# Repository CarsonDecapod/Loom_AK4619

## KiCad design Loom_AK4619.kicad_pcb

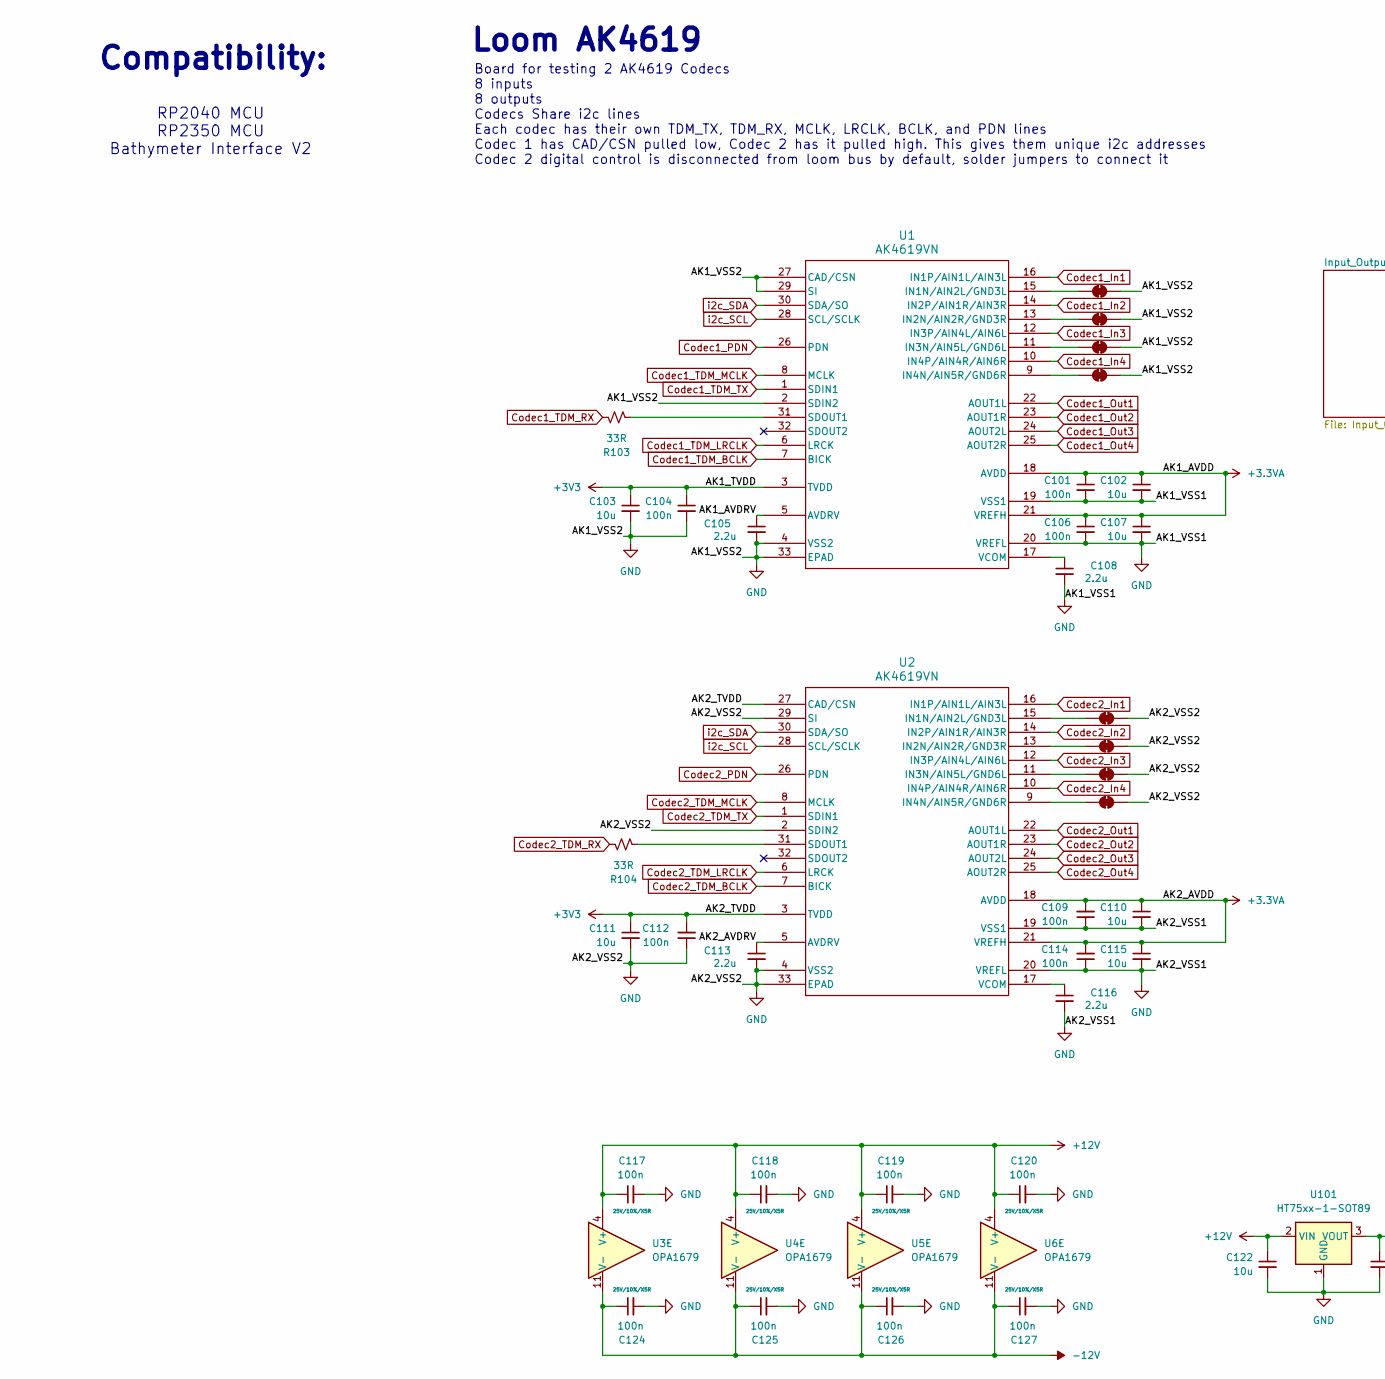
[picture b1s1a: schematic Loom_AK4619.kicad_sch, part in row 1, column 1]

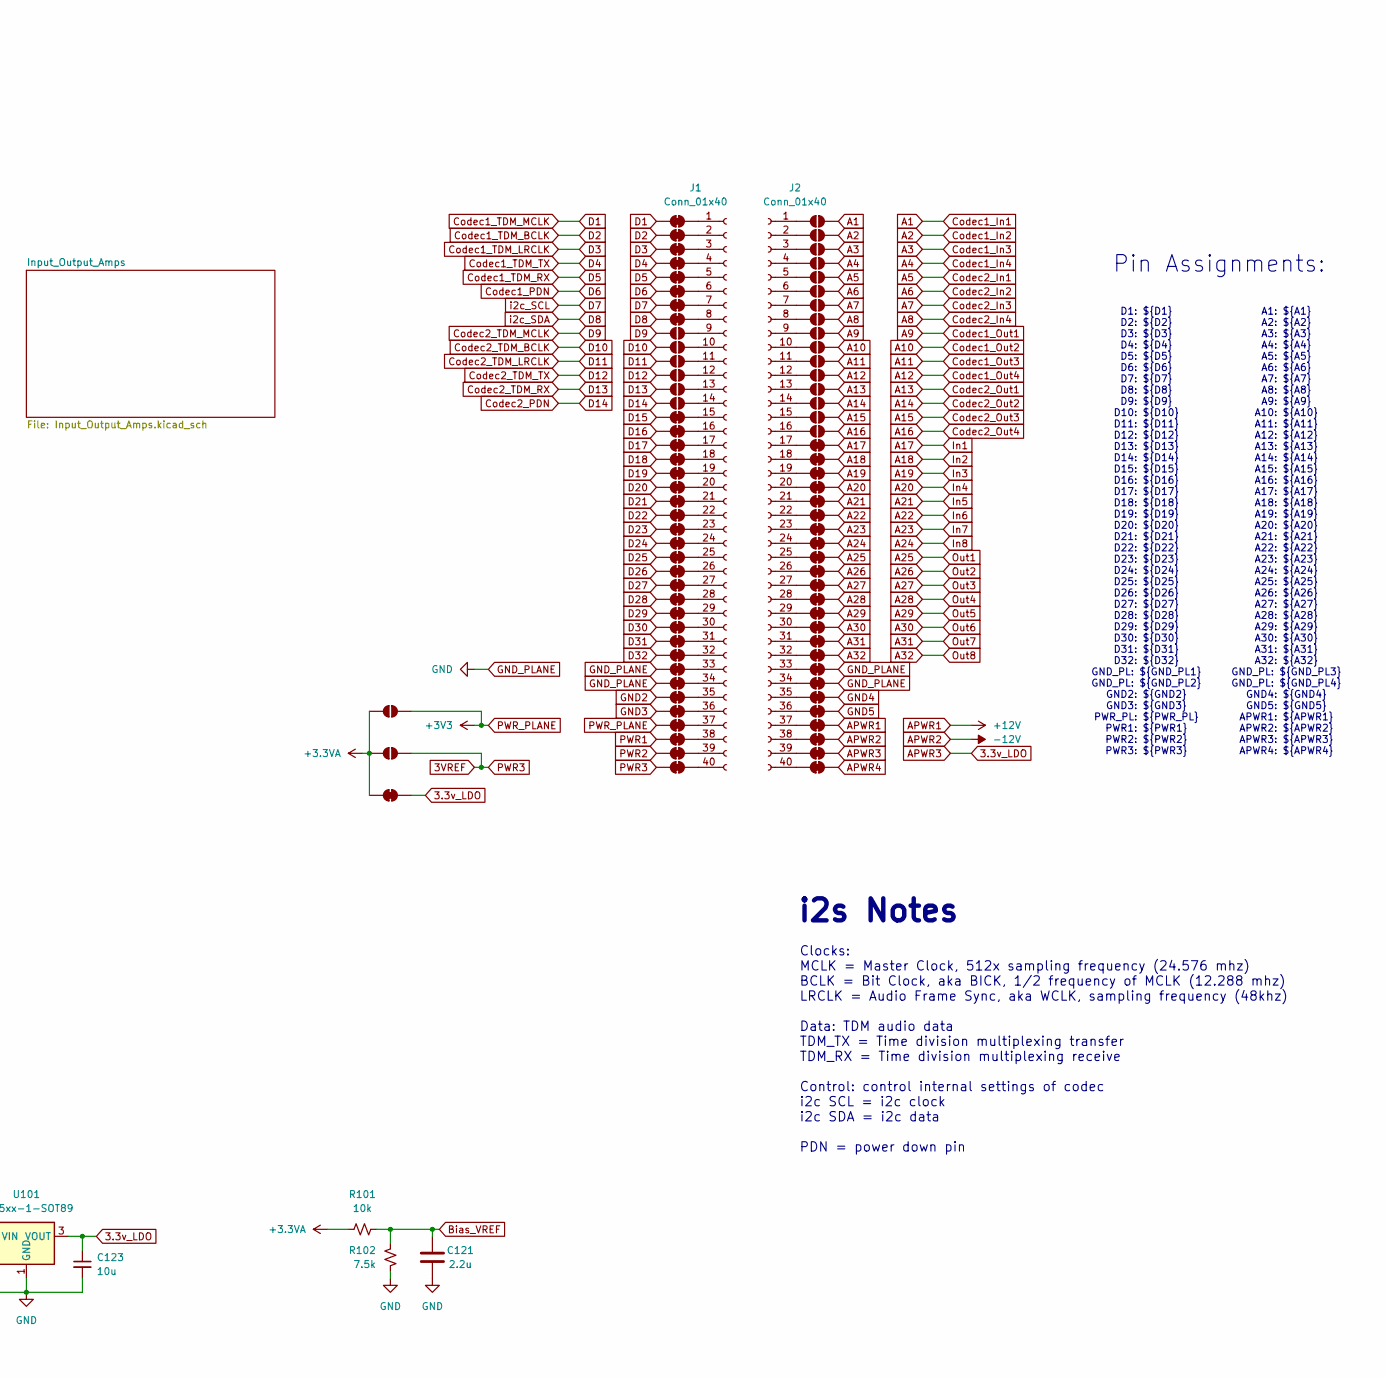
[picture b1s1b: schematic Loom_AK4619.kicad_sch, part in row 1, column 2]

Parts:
C101, C104, C106: 100n; C_0603_HandSolder; Rating 25V/10%/C0G; LCSC C1591
C102, C103, C107, C110, C111, C115, C122, C123: 10u; C_0805_HandSolder; Rating 25V/10%/C0G; LCSC C15850
C105, C108, C113, C116: 2.2u; C_0805_HandSolder; Rating 25V/10%/C0G; LCSC C377773
C109, C112, C114, C117, C118, C119, C120, C124, C125, C126, C127: 100n; C_0603_HandSolder; Rating 25V/10%/X5R; DigiKey 1276-1000-2-ND
C121: 2.2u; C_0805_HandSolder; LCSC C377773
J1, J2: Conn_01x40; PinHeader_1x40_P2.54mm_Vertical
JP101, JP102, JP103, JP104, JP105, JP106, JP107, JP108, JP115, JP116, JP117, JP118, JP119, JP120, JP121, JP122, JP123, JP124, JP125, JP126, JP127, JP128, JP129, JP130, JP131, JP132, JP133, JP134, JP135, JP136, JP137, JP138, JP139, JP140, JP157, JP158, JP159, JP160, JP161, JP162, JP163, JP164, JP165, JP166, JP167, JP168, JP169, JP170, JP171, JP172, JP173, JP174, JP175, JP176, JP177, JP178, JP179, JP180, JP181, JP182, JP183, JP184, JP186, JP187, JP189, JP190, JP191: SolderJumper-2_P1.3mm_Bridged_RoundedPad1.0x1.5mm
JP109, JP110, JP111, JP112, JP113, JP114, JP141, JP142, JP143, JP144, JP145, JP146, JP147, JP148, JP149, JP150, JP151, JP152, JP153, JP154, JP155, JP156, JP185, JP188: SolderJumper_2_Open; SolderJumper-2_P1.3mm_Open_Pad1.0x1.5mm
R101: 10k; R_0603_HandSolder; Rating 100mW/1%/Thin
R102: 7.5k; R_0603_HandSolder; Rating 100mW/1%/Thin
R103, R104: 33R; R_0603_HandSolder; Rating 100mW/1%/Thin
U1, U2: AK4619VN; QFN-32-1EP_5x5mm_P0.5mm_EP3.7x3.7mm_ThermalVias; LCSC C3034747
U3, U4, U5, U6: OPA1679; TSSOP-14_4.4x5mm_P0.65mm; MPN OPA1679
U101: HT75xx-1-SOT89; SOT-89-3

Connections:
3.3v_LDO: C123.1, JP179.1 (A), JP190.1 (A), U101.3 (VOUT)
3VREF: JP140.2 (B), JP188.2 (B)
+3.3VA: C101.1, C102.1, C106.1, C107.1, C109.2, C110.1, C114.2, C115.1, JP185.1 (A), JP188.1 (A), JP190.2 (B), R101.1, U1.18 (AVDD), U1.21 (VREFH), U2.18 (AVDD), U2.21 (VREFH)
/AK1_AVDRV: C105.1, U1.5 (AVDRV)
/AK2_AVDRV: C113.1, U2.5 (AVDRV)
A1: JP141.2 (B), U1.16 (IN1P/AIN1L/AIN3L); also elsewhere on the board
A2: JP142.2 (B), U1.14 (IN2P/AIN1R/AIN3R); also elsewhere on the board
A3: JP143.2 (B), U1.12 (IN3P/AIN4L/AIN6L); also elsewhere on the board
A4: JP144.2 (B), U1.10 (IN4P/AIN4R/AIN6R); also elsewhere on the board
A5: JP145.2 (B), U2.16 (IN1P/AIN1L/AIN3L); also elsewhere on the board
A6: JP146.2 (B), U2.14 (IN2P/AIN1R/AIN3R); also elsewhere on the board
A7: JP147.2 (B), U2.12 (IN3P/AIN4L/AIN6L); also elsewhere on the board
A8: JP148.2 (B), U2.10 (IN4P/AIN4R/AIN6R); also elsewhere on the board
A9: JP149.2 (B), U1.22 (AOUT1L); also elsewhere on the board
A10: JP150.2 (B), U1.23 (AOUT1R); also elsewhere on the board
A11: JP151.2 (B), U1.24 (AOUT2L); also elsewhere on the board
A12: JP152.2 (B), U1.25 (AOUT2R); also elsewhere on the board
A13: JP153.2 (B), U2.22 (AOUT1L); also elsewhere on the board
A14: JP154.2 (B), U2.23 (AOUT1R); also elsewhere on the board
A15: JP155.2 (B), U2.24 (AOUT2L); also elsewhere on the board
A16: JP156.2 (B), U2.25 (AOUT2R); also elsewhere on the board
A17: JP157.1 (A); also elsewhere on the board
A18: JP158.1 (A); also elsewhere on the board
A19: JP159.1 (A); also elsewhere on the board
A20: JP160.1 (A); also elsewhere on the board
A21: JP161.1 (A); also elsewhere on the board
A22: JP162.1 (A); also elsewhere on the board
A23: JP163.1 (A); also elsewhere on the board
A24: JP164.1 (A); also elsewhere on the board
A25: JP165.1 (A); also elsewhere on the board
A26: JP166.1 (A); also elsewhere on the board
A27: JP167.1 (A); also elsewhere on the board
A28: JP168.1 (A); also elsewhere on the board
A29: JP169.1 (A); also elsewhere on the board
A30: JP170.1 (A); also elsewhere on the board
A31: JP171.1 (A); also elsewhere on the board
A32: JP172.1 (A); also elsewhere on the board
APWR1: C117.1, C118.1, C119.1, C120.1, C122.1, JP177.1 (A), U3.4 (V+), U4.4 (V+), U5.4 (V+), U6.4 (V+), U101.2 (VIN)
APWR2: C124.1, C125.1, C126.1, C127.1, JP178.1 (A), U3.11 (V-), U4.11 (V-), U5.11 (V-), U6.11 (V-)
APWR4: JP180.1 (A)
Bias_VREF: C121.2, R101.2, R102.2, U3.3 (+), U3.5 (+), U3.10 (+), U4.3 (+), U4.5 (+), U4.10 (+), U5.5 (+), U5.10 (+), U5.12 (+), U6.5 (+), U6.10 (+), U6.12 (+); also elsewhere on the board
Codec1_PDN: JP106.2 (B), U1.26 (PDN)
Codec1_TDM_BCLK: JP102.2 (B), U1.7 (BICK)
Codec1_TDM_LRCLK: JP103.2 (B), U1.6 (LRCK)
Codec1_TDM_MCLK: JP101.2 (B), U1.8 (MCLK)
Codec1_TDM_RX: JP105.2 (B), R103.1
Codec1_TDM_TX: JP104.2 (B), U1.1 (SDIN1)
Codec2_PDN: JP114.1 (A), U2.26 (PDN)
Codec2_TDM_BCLK: JP110.1 (A), U2.7 (BICK)
Codec2_TDM_LRCLK: JP111.1 (A), U2.6 (LRCK)
Codec2_TDM_MCLK: JP109.1 (A), U2.8 (MCLK)
Codec2_TDM_RX: JP113.1 (A), R104.1
Codec2_TDM_TX: JP112.1 (A), U2.1 (SDIN1)
D7: JP107.2 (B), U1.28 (SCL/SCLK), U2.28 (SCL/SCLK)
D8: JP108.2 (B), U1.30 (SDA/SO), U2.30 (SDA/SO)
D15: JP115.2 (B)
D16: JP116.2 (B)
D17: JP117.2 (B)
D18: JP118.2 (B)
D19: JP119.2 (B)
D20: JP120.2 (B)
D21: JP121.2 (B)
D22: JP122.2 (B)
D23: JP123.2 (B)
D24: JP124.2 (B)
D25: JP125.2 (B)
D26: JP126.2 (B)
D27: JP127.2 (B)
D28: JP128.2 (B)
D29: JP129.2 (B)
D30: JP130.2 (B)
D31: JP131.2 (B)
D32: JP132.2 (B)
GND2: JP135.2 (B)
GND3: JP136.2 (B)
GND4: JP175.1 (A)
GND5: JP176.1 (A)
GND_PLANE: C101.2, C102.2, C103.2, C104.2, C105.2, C106.2, C107.2, C108.2, C109.1, C110.2, C111.2, C112.1, C113.2, C114.1, C115.2, C116.2, C117.2, C118.2, C119.2, C120.2, C121.1, C122.2, C123.2, C124.2, C125.2, C126.2, C127.2, JP133.2 (B), JP134.2 (B), JP173.1 (A), JP174.1 (A), JP181.1 (A), JP182.1 (A), JP183.1 (A), JP184.1 (A), JP186.1 (A), JP187.1 (A), JP189.1 (A), JP191.1 (A), R102.1, U1.2 (SDIN2), U1.4 (VSS2), U1.19 (VSS1), U1.20 (VREFL), U1.27 (CAD/CSN), U1.29 (SI), U1.33 (EPAD), U2.2 (SDIN2), U2.4 (VSS2), U2.19 (VSS1), U2.20 (VREFL), U2.29 (SI), U2.33 (EPAD), U101.1 (GND)
unnamed 78: U3.1; also elsewhere on the board
unnamed 79: U3.7; also elsewhere on the board
unnamed 80: U3.8; also elsewhere on the board
unnamed 82: U4.1; also elsewhere on the board
unnamed 83: U4.7; also elsewhere on the board
unnamed 84: U4.8; also elsewhere on the board
unnamed 87: U5.7; also elsewhere on the board
unnamed 88: U5.8; also elsewhere on the board
unnamed 89: U5.14; also elsewhere on the board
unnamed 91: U6.7; also elsewhere on the board
unnamed 92: U6.8; also elsewhere on the board
unnamed 93: U6.14; also elsewhere on the board
unnamed: J1.1, JP101.1 (A)
unnamed: J1.2, JP102.1 (A)
unnamed: J1.3, JP103.1 (A)
unnamed: J1.4, JP104.1 (A)
unnamed: J1.5, JP105.1 (A)
unnamed: J1.6, JP106.1 (A)
unnamed: J1.7, JP107.1 (A)
unnamed: J1.8, JP108.1 (A)
unnamed: J1.9, JP109.2 (B)
unnamed: J1.10, JP110.2 (B)
unnamed: J1.11, JP111.2 (B)
unnamed: J1.12, JP112.2 (B)
unnamed: J1.13, JP113.2 (B)
unnamed: J1.14, JP114.2 (B)
unnamed: J1.15, JP115.1 (A)
unnamed: J1.16, JP116.1 (A)
unnamed: J1.17, JP117.1 (A)
unnamed: J1.18, JP118.1 (A)
unnamed: J1.19, JP119.1 (A)
unnamed: J1.20, JP120.1 (A)
unnamed: J1.21, JP121.1 (A)
unnamed: J1.22, JP122.1 (A)
unnamed: J1.23, JP123.1 (A)
unnamed: J1.24, JP124.1 (A)
unnamed: J1.25, JP125.1 (A)
unnamed: J1.26, JP126.1 (A)
unnamed: J1.27, JP127.1 (A)
unnamed: J1.28, JP128.1 (A)
unnamed: J1.29, JP129.1 (A)
unnamed: J1.30, JP130.1 (A)
unnamed: J1.31, JP131.1 (A)
unnamed: J1.32, JP132.1 (A)
unnamed: J1.33, JP133.1 (A)
unnamed: J1.34, JP134.1 (A)
unnamed: J1.35, JP135.1 (A)
unnamed: J1.36, JP136.1 (A)
unnamed: J1.37, JP137.1 (A)
unnamed: J1.38, JP138.1 (A)
unnamed: J1.39, JP139.1 (A)
unnamed: J1.40, JP140.1 (A)
unnamed: J2.1, JP141.1 (A)
unnamed: J2.2, JP142.1 (A)
unnamed: J2.3, JP143.1 (A)
unnamed: J2.4, JP144.1 (A)
unnamed: J2.5, JP145.1 (A)
unnamed: J2.6, JP146.1 (A)
unnamed: J2.7, JP147.1 (A)
unnamed: J2.8, JP148.1 (A)
unnamed: J2.9, JP149.1 (A)
unnamed: J2.10, JP150.1 (A)
unnamed: J2.11, JP151.1 (A)
unnamed: J2.12, JP152.1 (A)
unnamed: J2.13, JP153.1 (A)
unnamed: J2.14, JP154.1 (A)
unnamed: J2.15, JP155.1 (A)
unnamed: J2.16, JP156.1 (A)
unnamed: J2.17, JP157.2 (B)
unnamed: J2.18, JP158.2 (B)
unnamed: J2.19, JP159.2 (B)
unnamed: J2.20, JP160.2 (B)
unnamed: J2.21, JP161.2 (B)
unnamed: J2.22, JP162.2 (B)
unnamed: J2.23, JP163.2 (B)
unnamed: J2.24, JP164.2 (B)
unnamed: J2.25, JP165.2 (B)
unnamed: J2.26, JP166.2 (B)
unnamed: J2.27, JP167.2 (B)
unnamed: J2.28, JP168.2 (B)
unnamed: J2.29, JP169.2 (B)
unnamed: J2.30, JP170.2 (B)
unnamed: J2.31, JP171.2 (B)
unnamed: J2.32, JP172.2 (B)
unnamed: J2.33, JP173.2 (B)
unnamed: J2.34, JP174.2 (B)
unnamed: J2.35, JP175.2 (B)
unnamed: J2.36, JP176.2 (B)
unnamed: J2.37, JP177.2 (B)
unnamed: J2.38, JP178.2 (B)
unnamed: J2.39, JP179.2 (B)
unnamed: J2.40, JP180.2 (B)
unnamed: JP181.2 (B), U1.15 (IN1N/AIN2L/GND3L)
unnamed: JP182.2 (B), U1.13 (IN2N/AIN2R/GND3R)
unnamed: JP183.2 (B), U1.11 (IN3N/AIN5L/GND6L)
unnamed: JP184.2 (B), U1.9 (IN4N/AIN5R/GND6R)
unnamed: JP186.2 (B), U2.15 (IN1N/AIN2L/GND3L)
unnamed: JP187.2 (B), U2.13 (IN2N/AIN2R/GND3R)
unnamed: JP189.2 (B), U2.11 (IN3N/AIN5L/GND6L)
unnamed: JP191.2 (B), U2.9 (IN4N/AIN5R/GND6R)
unnamed: R103.2, U1.31 (SDOUT1)
unnamed: C108.1, U1.17 (VCOM)
unnamed: R104.2, U2.31 (SDOUT1)
unnamed: C116.1, U2.17 (VCOM)
unnamed 186: U3.2 (-); also elsewhere on the board
unnamed 187: U3.6 (-); also elsewhere on the board
unnamed 188: U3.9 (-); also elsewhere on the board
unnamed 190: U4.2 (-); also elsewhere on the board
unnamed 191: U4.6 (-); also elsewhere on the board
unnamed 192: U4.9 (-); also elsewhere on the board
unnamed 195: U5.6 (-); also elsewhere on the board
unnamed 196: U5.9 (-); also elsewhere on the board
unnamed 197: U5.13 (-); also elsewhere on the board
unnamed 199: U6.6 (-); also elsewhere on the board
unnamed 200: U6.9 (-); also elsewhere on the board
unnamed 201: U6.13 (-); also elsewhere on the board
PWR1: JP138.2 (B)
PWR2: JP139.2 (B)
PWR_PLANE: C103.1, C104.1, C111.1, C112.2, JP137.2 (B), JP185.2 (B), U1.3 (TVDD), U2.3 (TVDD), U2.27 (CAD/CSN)

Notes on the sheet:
Pin Assignments:
A1: ${A1} A2: ${A2} A3: ${A3} A4: ${A4} A5: ${A5} A6: ${A6} A7: ${A7} A8: ${A8} A9: ${A9} A10: ${A10} A11: ${A11} A12: ${A12} A13: ${A13} A14: ${A14} A15: ${A15} A16: ${A16} A17: ${A17} A18: ${A18} A19: ${A19} A20: ${A20} A21: ${A21} A22: ${A22} A23: ${A23} A24: ${A24} A25: ${A25} A26: ${A26} A27: 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
Clocks: MCLK = Master Clock, 512x sampling frequency (24.576 mhz) BCLK = Bit Clock, aka BICK, 1/2 frequency of MCLK (12.288 mhz) LRCLK = Audio Frame Sync, aka WCLK, sampling frequency (48khz) Data: TDM audio data TDM_TX = Time division multiplexing transfer TDM_RX = Time division multiplexing recei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
Loom AK4619
i2s Notes
Board for testing 2 AK4619 Codecs 8 inputs 8 outputs Codecs Share i2c lines Each codec has their own TDM_TX, TDM_RX, MCLK, LRCLK, BCLK, and PDN lines Codec 1 has CAD/CSN pulled low, Codec 2 has it pulled high. This gives them unique i2c addresses Codec 2 digital control is disconnected from loom bu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
D1: ${D1} D2: ${D2} D3: ${D3} D4: ${D4} D5: ${D5} D6: ${D6} D7: ${D7} D8: ${D8} D9: ${D9} D10: ${D10} D11: ${D11} D12: ${D12} D13: ${D13} D14: ${D14} D15: ${D15} D16: ${D16} D17: ${D17} D18: ${D18} D19: ${D19} D20: ${D20} D21: ${D21} D22: ${D22} D23: ${D23} D24: ${D24} D25: ${D25} D26: ${D26} D27: 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
Compatibility:
RP2040 MCU RP2350 MCU Bathymeter Interface V2

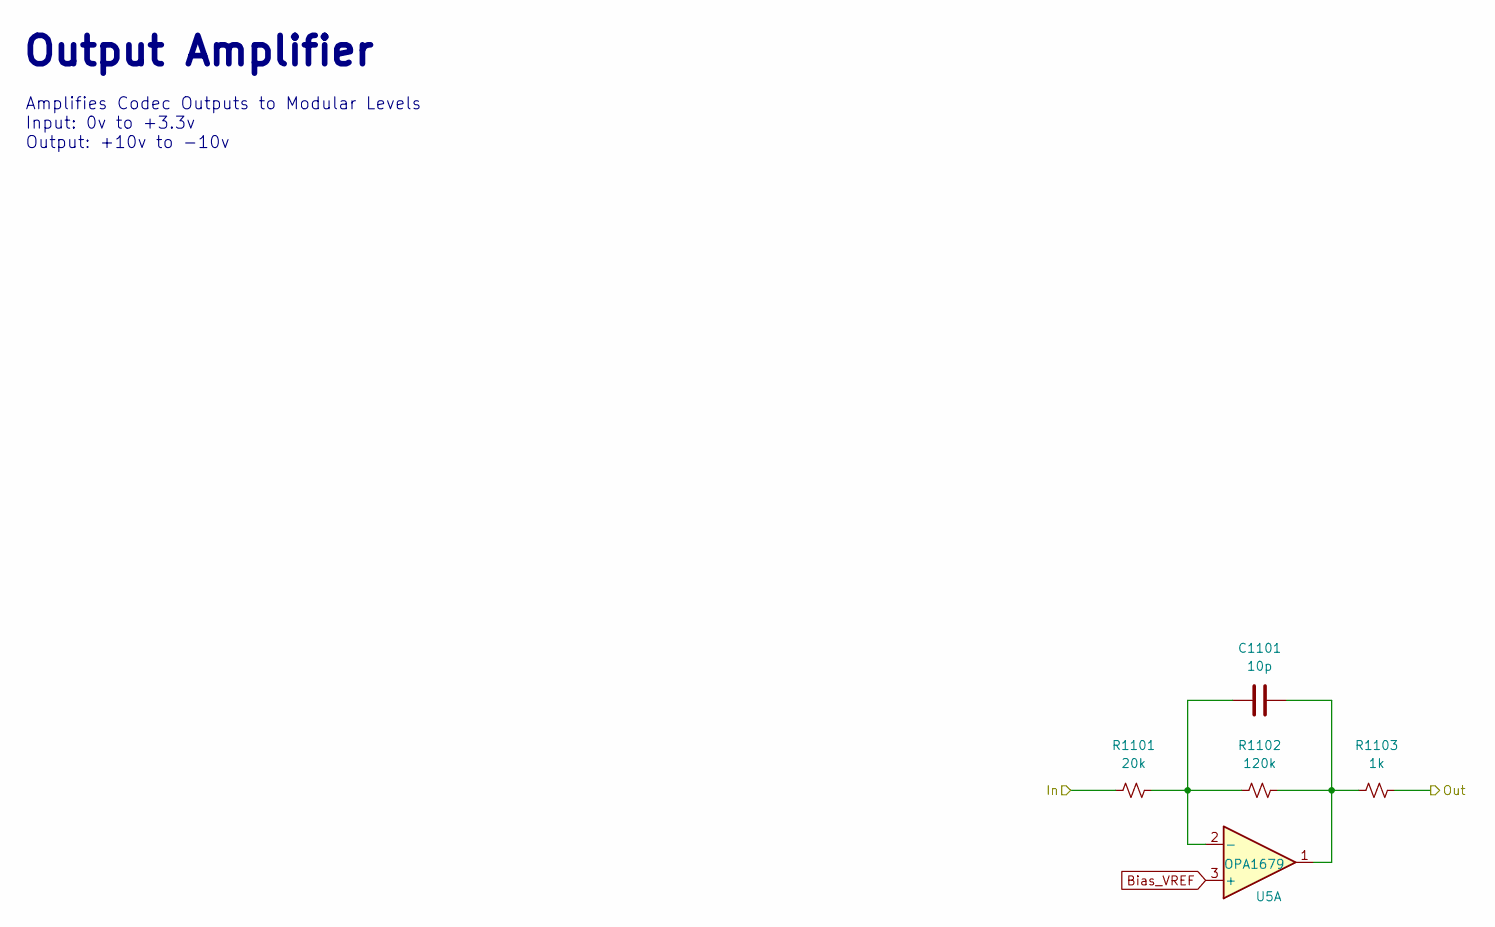
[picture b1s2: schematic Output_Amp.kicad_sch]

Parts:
C1101: 10p; C_0603_HandSolder; LCSC C1634
R1101: 20k; R_0603_HandSolder; Rating 100mW/1%/Thin
R1102: 120k; R_0603_HandSolder; Rating 100mW/1%/Thin
R1103: 1k; R_0603_HandSolder; Rating 100mW/1%/Thin
U5: OPA1679; TSSOP-14_4.4x5mm_P0.65mm; MPN OPA1679

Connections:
A9: R1101.1; also elsewhere on the board
A25: R1103.2; also elsewhere on the board
Bias_VREF: U5.3 (+), U5.5 (+), U5.10 (+), U5.12 (+); also elsewhere on the board
unnamed: C1101.1, R1102.2, R1103.1, U5.1
unnamed 87: U5.7; also elsewhere on the board
unnamed 88: U5.8; also elsewhere on the board
unnamed 89: U5.14; also elsewhere on the board
unnamed: C1101.2, R1101.2, R1102.1, U5.2 (-)
unnamed 195: U5.6 (-); also elsewhere on the board
unnamed 196: U5.9 (-); also elsewhere on the board
unnamed 197: U5.13 (-); also elsewhere on the board

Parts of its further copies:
C1201, C1301, C1401, C1501, C1601, C1701, C1801: 10p; C_0603_HandSolder; LCSC C1634
R1201, R1301, R1401, R1501, R1601, R1701, R1801: 20k; R_0603_HandSolder; Rating 100mW/1%/Thin
R1202, R1302, R1402, R1502, R1602, R1702, R1802: 120k; R_0603_HandSolder; Rating 100mW/1%/Thin
R1203, R1303, R1403, R1503, R1603, R1703, R1803: 1k; R_0603_HandSolder; Rating 100mW/1%/Thin

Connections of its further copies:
A10: R1201.1; also elsewhere on the board
A11: R1301.1; also elsewhere on the board
A12: R1401.1; also elsewhere on the board
A13: R1501.1; also elsewhere on the board
A14: R1601.1; also elsewhere on the board
A15: R1701.1; also elsewhere on the board
A16: R1801.1; also elsewhere on the board
A26: R1203.2; also elsewhere on the board
A27: R1303.2; also elsewhere on the board
A28: R1403.2; also elsewhere on the board
A29: R1503.2; also elsewhere on the board
A30: R1603.2; also elsewhere on the board
A31: R1703.2; also elsewhere on the board
A32: R1803.2; also elsewhere on the board
unnamed 87: C1201.1, R1202.2, R1203.1; also elsewhere on the board
unnamed 88: C1301.1, R1302.2, R1303.1; also elsewhere on the board
unnamed 89: C1401.1, R1402.2, R1403.1; also elsewhere on the board
unnamed 90: C1501.1, R1502.2, R1503.1; also elsewhere on the board
unnamed 91: C1601.1, R1602.2, R1603.1; also elsewhere on the board
unnamed 92: C1701.1, R1702.2, R1703.1; also elsewhere on the board
unnamed 93: C1801.1, R1802.2, R1803.1; also elsewhere on the board
unnamed 195: C1201.2, R1201.2, R1202.1; also elsewhere on the board
unnamed 196: C1301.2, R1301.2, R1302.1; also elsewhere on the board
unnamed 197: C1401.2, R1401.2, R1402.1; also elsewhere on the board
unnamed 198: C1501.2, R1501.2, R1502.1; also elsewhere on the board
unnamed 199: C1601.2, R1601.2, R1602.1; also elsewhere on the board
unnamed 200: C1701.2, R1701.2, R1702.1; also elsewhere on the board
unnamed 201: C1801.2, R1801.2, R1802.1; also elsewhere on the board

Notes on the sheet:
Amplifies Codec Outputs to Modular Levels Input: 0v to +3.3v Output: +10v to -10v
Output Amplifier

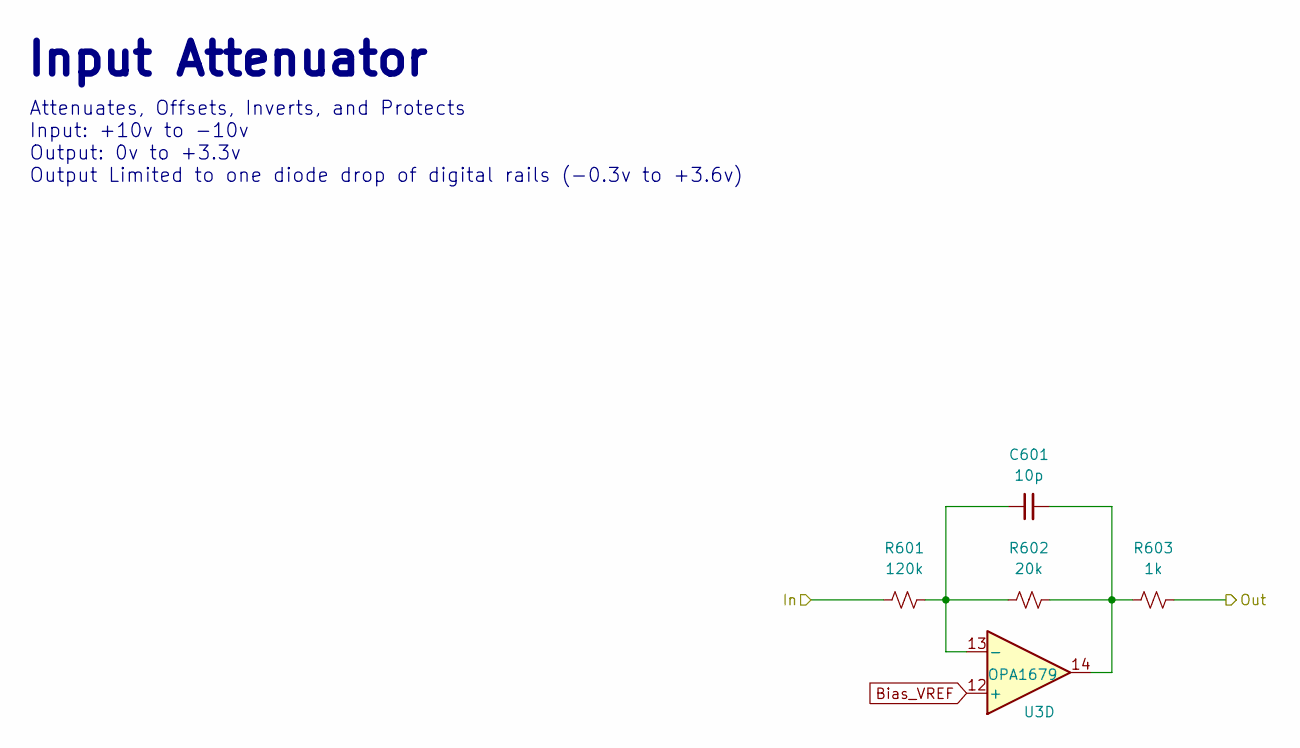
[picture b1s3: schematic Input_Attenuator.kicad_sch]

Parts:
C601: 10p; C_0603_HandSolder; Rating 25V/10%/C0G; LCSC C1634
R601: 120k; R_0603_HandSolder; Rating 100mW/1%/Thin
R602: 20k; R_0603_HandSolder; Rating 100mW/1%/Thin
R603: 1k; R_0603_HandSolder; Rating 100mW/1%/Thin
U3: OPA1679; TSSOP-14_4.4x5mm_P0.65mm; MPN OPA1679

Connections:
A4: R603.2; also elsewhere on the board
A20: R601.1; also elsewhere on the board
Bias_VREF: U3.3 (+), U3.5 (+), U3.10 (+), U3.12 (+); also elsewhere on the board
unnamed 78: U3.1; also elsewhere on the board
unnamed 79: U3.7; also elsewhere on the board
unnamed 80: U3.8; also elsewhere on the board
unnamed: C601.2, R602.2, R603.1, U3.14
unnamed 186: U3.2 (-); also elsewhere on the board
unnamed 187: U3.6 (-); also elsewhere on the board
unnamed 188: U3.9 (-); also elsewhere on the board
unnamed: C601.1, R601.2, R602.1, U3.13 (-)

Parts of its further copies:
C301, C401, C501, C701, C801, C901, C1001: 10p; C_0603_HandSolder; Rating 25V/10%/C0G; LCSC C1634
R301, R401, R501, R701, R801, R901, R1001: 120k; R_0603_HandSolder; Rating 100mW/1%/Thin
R302, R402, R502, R702, R802, R902, R1002: 20k; R_0603_HandSolder; Rating 100mW/1%/Thin
R303, R403, R503, R703, R803, R903, R1003: 1k; R_0603_HandSolder; Rating 100mW/1%/Thin

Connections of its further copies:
A1: R303.2; also elsewhere on the board
A2: R403.2; also elsewhere on the board
A3: R503.2; also elsewhere on the board
A5: R703.2; also elsewhere on the board
A6: R803.2; also elsewhere on the board
A7: R903.2; also elsewhere on the board
A8: R1003.2; also elsewhere on the board
A17: R301.1; also elsewhere on the board
A18: R401.1; also elsewhere on the board
A19: R501.1; also elsewhere on the board
A21: R701.1; also elsewhere on the board
A22: R801.1; also elsewhere on the board
A23: R901.1; also elsewhere on the board
A24: R1001.1; also elsewhere on the board
unnamed 78: C301.2, R302.2, R303.1; also elsewhere on the board
unnamed 79: C401.2, R402.2, R403.1; also elsewhere on the board
unnamed 80: C501.2, R502.2, R503.1; also elsewhere on the board
unnamed 82: C701.2, R702.2, R703.1; also elsewhere on the board
unnamed 83: C801.2, R802.2, R803.1; also elsewhere on the board
unnamed 84: C901.2, R902.2, R903.1; also elsewhere on the board
unnamed 85: C1001.2, R1002.2, R1003.1; also elsewhere on the board
unnamed 186: C301.1, R301.2, R302.1; also elsewhere on the board
unnamed 187: C401.1, R401.2, R402.1; also elsewhere on the board
unnamed 188: C501.1, R501.2, R502.1; also elsewhere on the board
unnamed 190: C701.1, R701.2, R702.1; also elsewhere on the board
unnamed 191: C801.1, R801.2, R802.1; also elsewhere on the board
unnamed 192: C901.1, R901.2, R902.1; also elsewhere on the board
unnamed 193: C1001.1, R1001.2, R1002.1; also elsewhere on the board

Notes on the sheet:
Attenuates, Offsets, Inverts, and Protects Input: +10v to -10v Output: 0v to +3.3v Output Limited to one diode drop of digital rails (-0.3v to +3.6v)
Input Attenuator

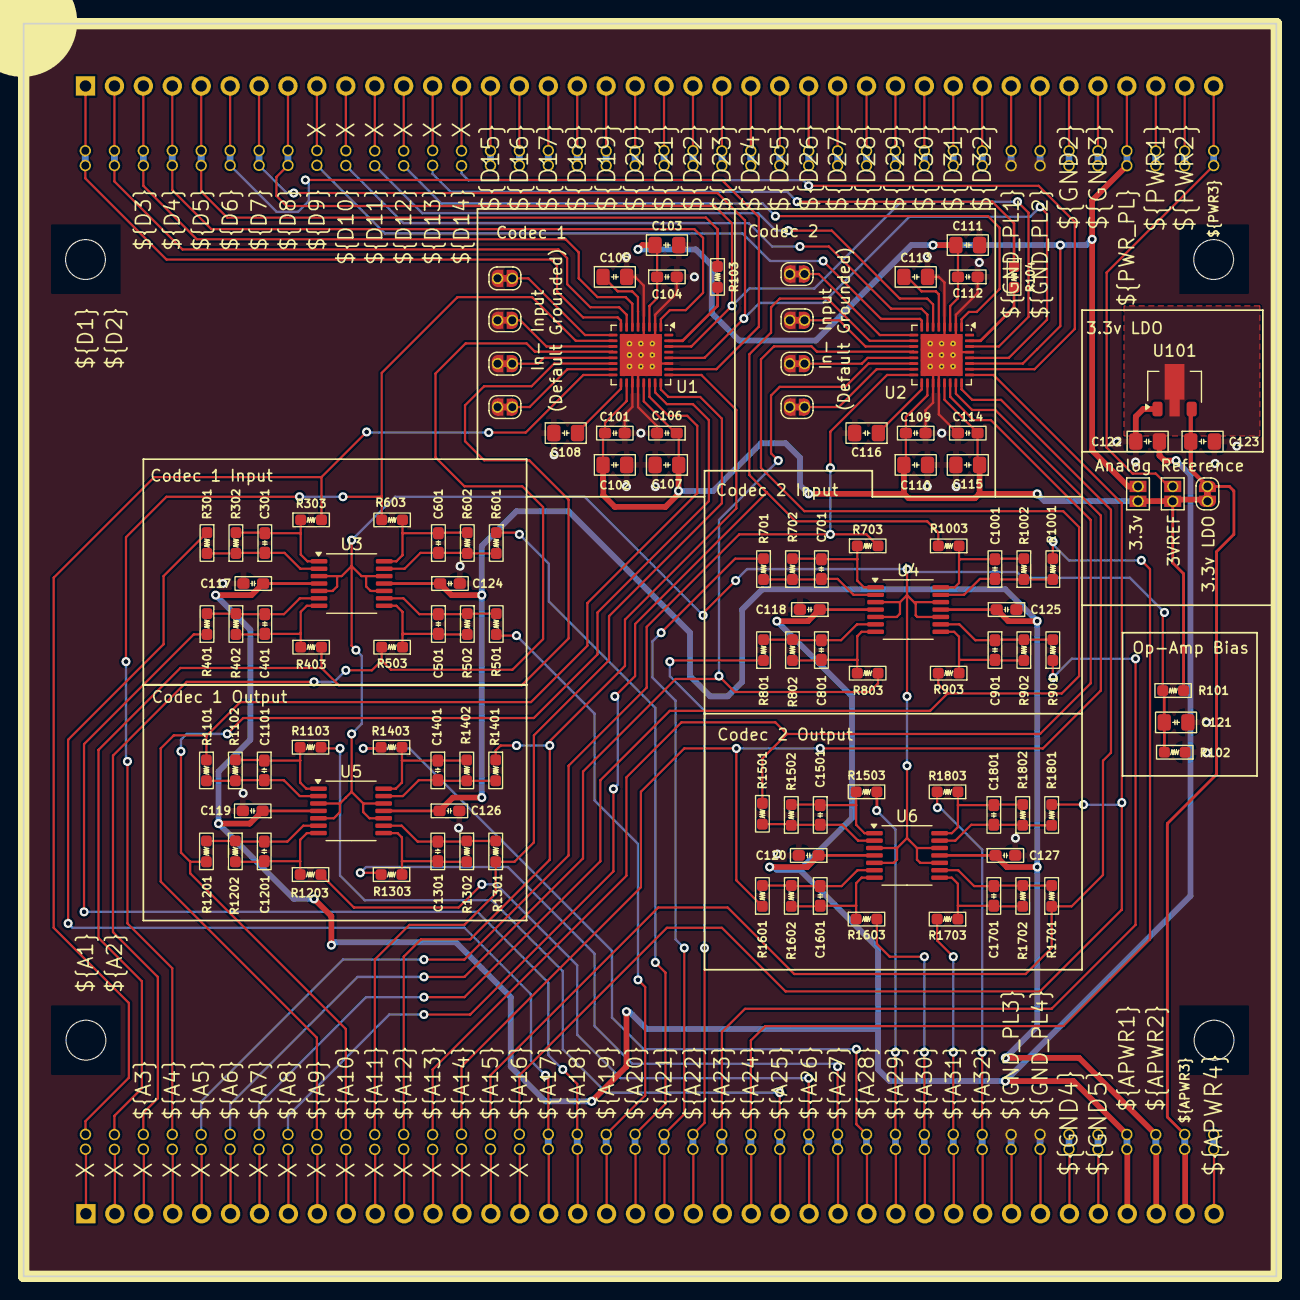
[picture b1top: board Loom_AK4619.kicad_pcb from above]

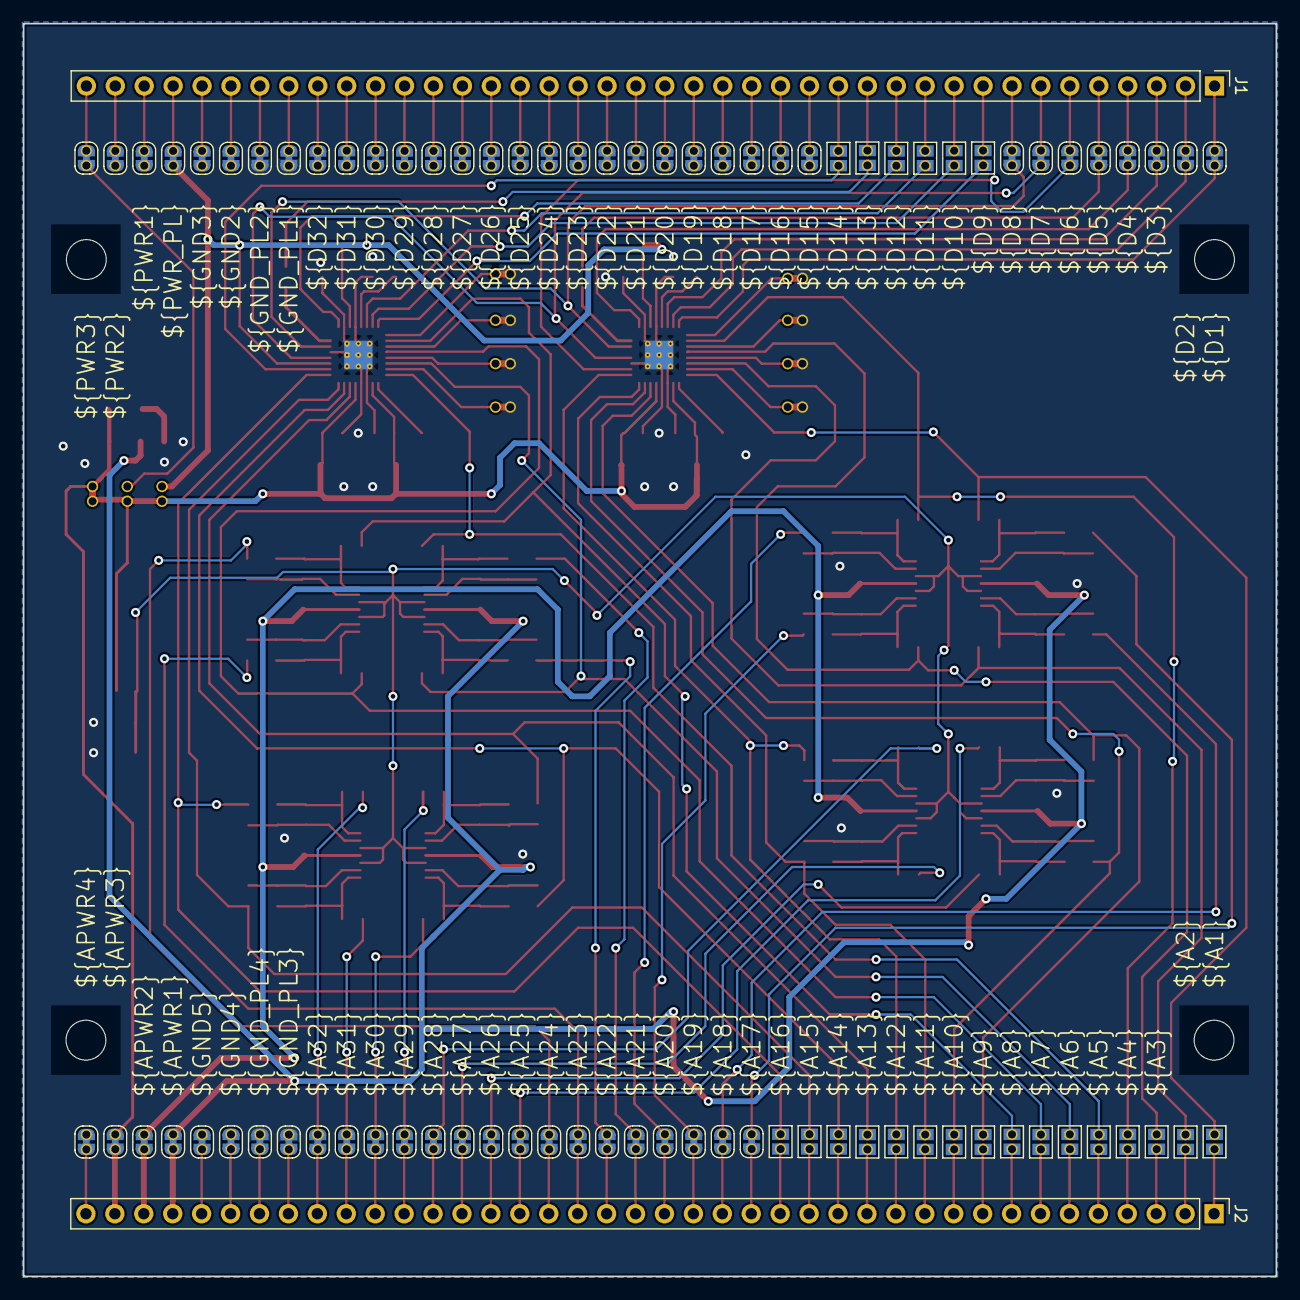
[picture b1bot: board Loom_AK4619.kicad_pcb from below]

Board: 2 copper layers, 110.0 x 110.0 mm, 195 parts (82 on the bottom side), 180 nets.

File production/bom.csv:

Designator,Footprint,Quantity,Value,LCSC Part #
"C1001, C1101, C1201, C1301, C1401, C1501, C1601, C1701, C1801, C301, C401, C501, C601, C701, C801, C901",C_0603_HandSolder,16,10p,C1634
"C101, C104, C106, C109, C112, C114, C117, C118, C119, C120, C124, C125, C126, C127",C_0603_HandSolder,14,100n,C1591
"C102, C103, C107, C110, C111, C115, C122, C123",C_0805_HandSolder,8,10u,C15850
"C105, C108, C113, C116, C121",C_0805_HandSolder,5,2.2u,C377773
"J1, J2",PinHeader_1x40_P2.54mm_Vertical,2,Conn_01x40,
"R1001, R1102, R1202, R1302, R1402, R1502, R1602, R1702, R1802, R301, R401, R501, R601, R701, R801, R901",R_0603_HandSolder,16,120k,
"R1002, R1101, R1201, R1301, R1401, R1501, R1601, R1701, R1801, R302, R402, R502, R602, R702, R802, R902",R_0603_HandSolder,16,20k,
"R1003, R1103, R1203, R1303, R1403, R1503, R1603, R1703, R1803, R303, R403, R503, R603, R703, R803, R903",R_0603_HandSolder,16,1k,
R101,R_0603_HandSolder,1,10k,
R102,R_0603_HandSolder,1,7.5k,
"R103, R104",R_0603_HandSolder,2,33R,
"U1, U2",QFN-32-1EP_5x5mm_P0.5mm_EP3.7x3.7mm_ThermalVias,2,AK4619VN,C3034747
U101,SOT-89-3,1,HT75xx-1-SOT89,
"U3, U4, U5, U6",TSSOP-14_4.4x5mm_P0.65mm,4,OPA1679,OPA1679

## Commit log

2025-01-08 AK4619 Routed, Should be ready to order
2025-01-09 Slight routing updates
2025-01-11 Added 33R resistors to SDOUT
    Added 33R resistors to SDOUT to decrease slew rate slightly to reduce radiated emissions.
2025-02-09 Version 1 ready to order
